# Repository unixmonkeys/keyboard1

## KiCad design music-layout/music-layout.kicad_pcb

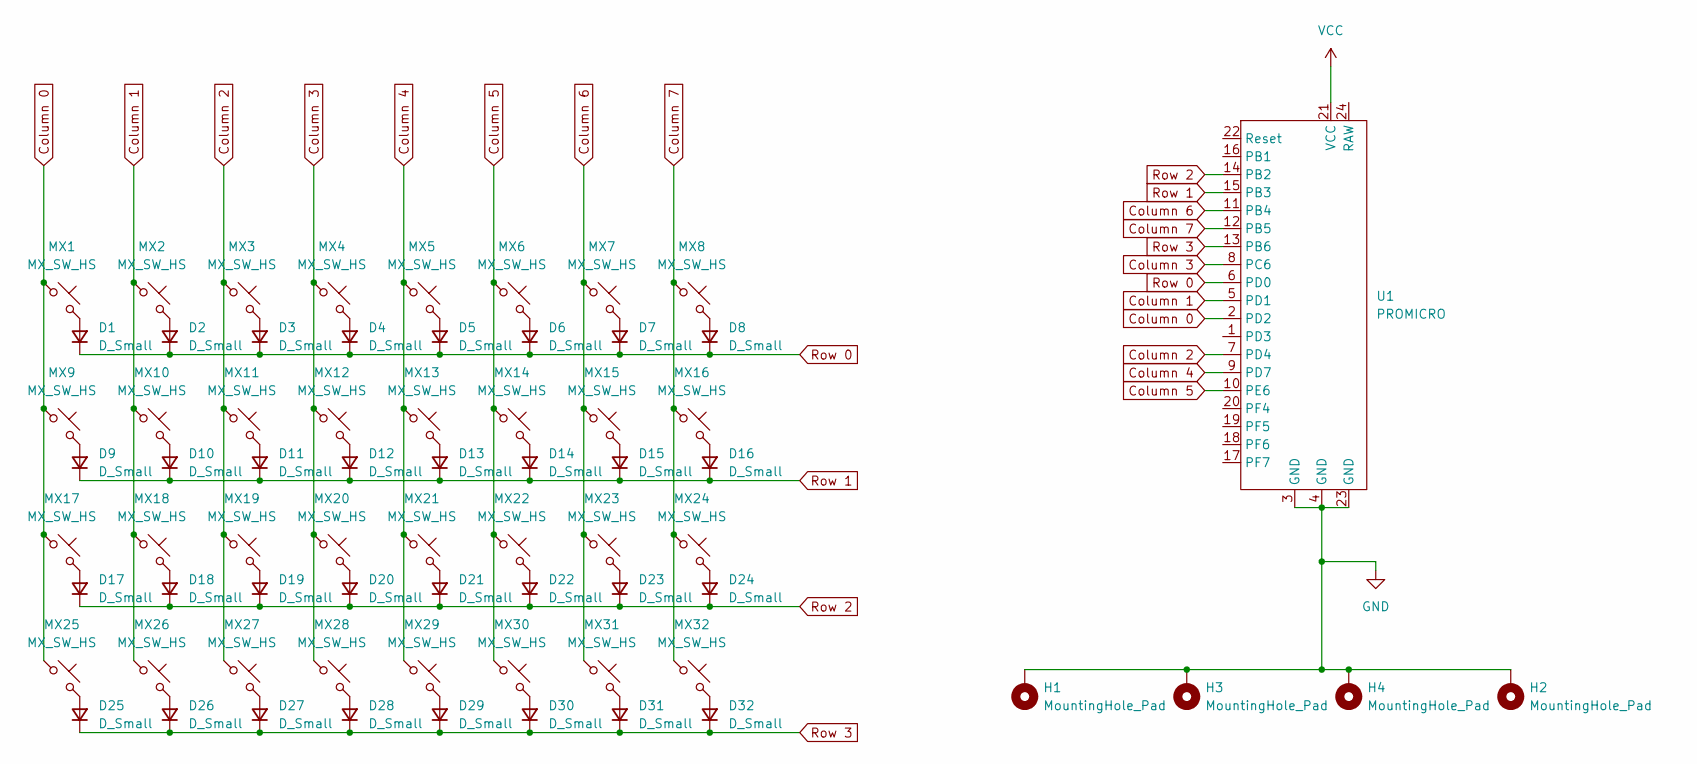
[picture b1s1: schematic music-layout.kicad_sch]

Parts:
D1, D2, D3, D4, D5, D6, D7, D8, D9, D10, D11, D12, D13, D14, D15, D16, D17, D18, D19, D20, D21, D22, D23, D24, D25, D26, D27, D28, D29, D30, D31, D32: D_Small; D_DO-35_SOD27_P7.62mm_Horizontal
H1, H2, H3, H4: MountingHole_Pad; MountingHole_2.2mm_M2_Pad_Via
MX1, MX2, MX3, MX4, MX5, MX6, MX7, MX8, MX9, MX10, MX11, MX12, MX13, MX14, MX15, MX16, MX17, MX18, MX19, MX20, MX21, MX22, MX23, MX24, MX25, MX26, MX27, MX28, MX29, MX30, MX31, MX32: MX_SW_HS; SW_MX_HS_CPG151101S11_1u
U1: PROMICRO; Sparkfun_Pro_Micro

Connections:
Column 0: MX1.1, MX9.1, MX17.1, MX25.1, U1.2 (PD2)
Column 1: MX2.1, MX10.1, MX18.1, MX26.1, U1.5 (PD1)
Column 2: MX3.1, MX11.1, MX19.1, MX27.1, U1.7 (PD4)
Column 3: MX4.1, MX12.1, MX20.1, MX28.1, U1.8 (PC6)
Column 4: MX5.1, MX13.1, MX21.1, MX29.1, U1.9 (PD7)
Column 5: MX6.1, MX14.1, MX22.1, MX30.1, U1.10 (PE6)
Column 6: MX7.1, MX15.1, MX23.1, MX31.1, U1.11 (PB4)
Column 7: MX8.1, MX16.1, MX24.1, MX32.1, U1.12 (PB5)
GND: H1.1, H2.1, H3.1, H4.1, U1.3 (GND), U1.4 (GND), U1.23 (GND)
unnamed: D1.2 (A), MX1.2
unnamed: D2.2 (A), MX2.2
unnamed: D3.2 (A), MX3.2
unnamed: D4.2 (A), MX4.2
unnamed: D5.2 (A), MX5.2
unnamed: D6.2 (A), MX6.2
unnamed: D7.2 (A), MX7.2
unnamed: D8.2 (A), MX8.2
unnamed: D9.2 (A), MX9.2
unnamed: D10.2 (A), MX10.2
unnamed: D11.2 (A), MX11.2
unnamed: D12.2 (A), MX12.2
unnamed: D13.2 (A), MX13.2
unnamed: D14.2 (A), MX14.2
unnamed: D15.2 (A), MX15.2
unnamed: D16.2 (A), MX16.2
unnamed: D17.2 (A), MX17.2
unnamed: D18.2 (A), MX18.2
unnamed: D19.2 (A), MX19.2
unnamed: D20.2 (A), MX20.2
unnamed: D21.2 (A), MX21.2
unnamed: D22.2 (A), MX22.2
unnamed: D23.2 (A), MX23.2
unnamed: D24.2 (A), MX24.2
unnamed: D25.2 (A), MX25.2
unnamed: D26.2 (A), MX26.2
unnamed: D27.2 (A), MX27.2
unnamed: D28.2 (A), MX28.2
unnamed: D29.2 (A), MX29.2
unnamed: D30.2 (A), MX30.2
unnamed: D31.2 (A), MX31.2
unnamed: D32.2 (A), MX32.2
Row 0: D1.1 (K), D2.1 (K), D3.1 (K), D4.1 (K), D5.1 (K), D6.1 (K), D7.1 (K), D8.1 (K), U1.6 (PD0)
Row 1: D9.1 (K), D10.1 (K), D11.1 (K), D12.1 (K), D13.1 (K), D14.1 (K), D15.1 (K), D16.1 (K), U1.15 (PB3)
Row 2: D17.1 (K), D18.1 (K), D19.1 (K), D20.1 (K), D21.1 (K), D22.1 (K), D23.1 (K), D24.1 (K), U1.14 (PB2)
Row 3: D25.1 (K), D26.1 (K), D27.1 (K), D28.1 (K), D29.1 (K), D30.1 (K), D31.1 (K), D32.1 (K), U1.13 (PB6)
VCC: U1.21 (VCC)

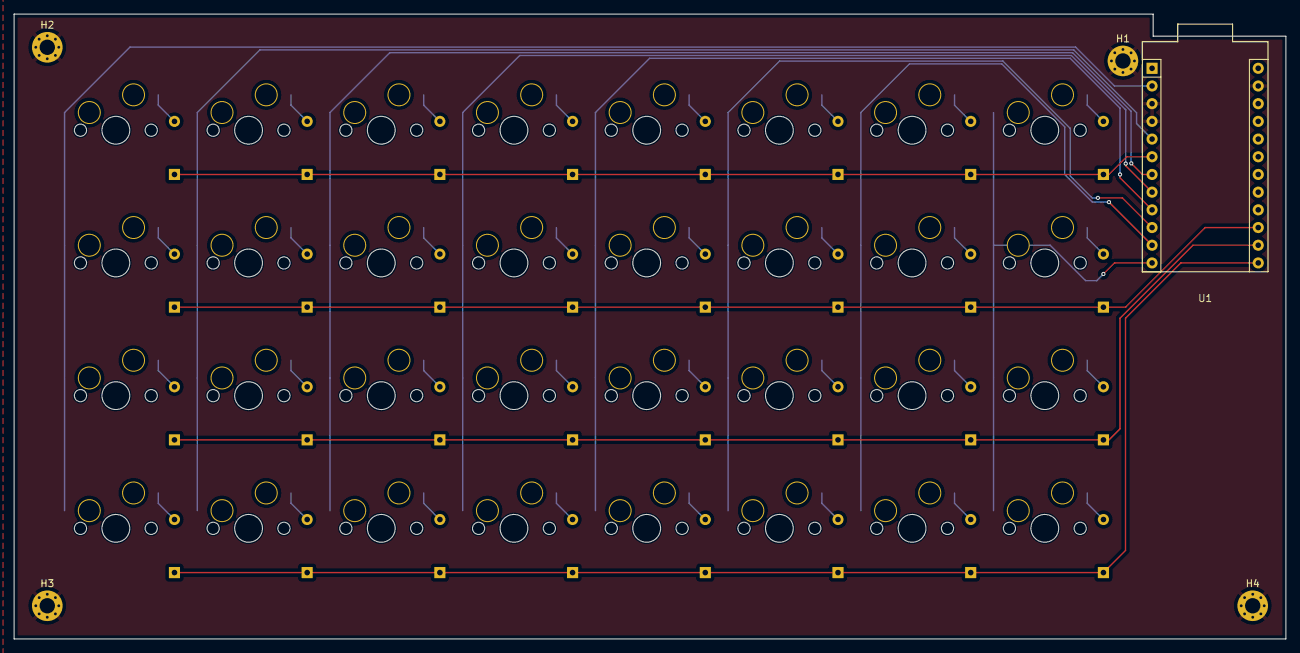
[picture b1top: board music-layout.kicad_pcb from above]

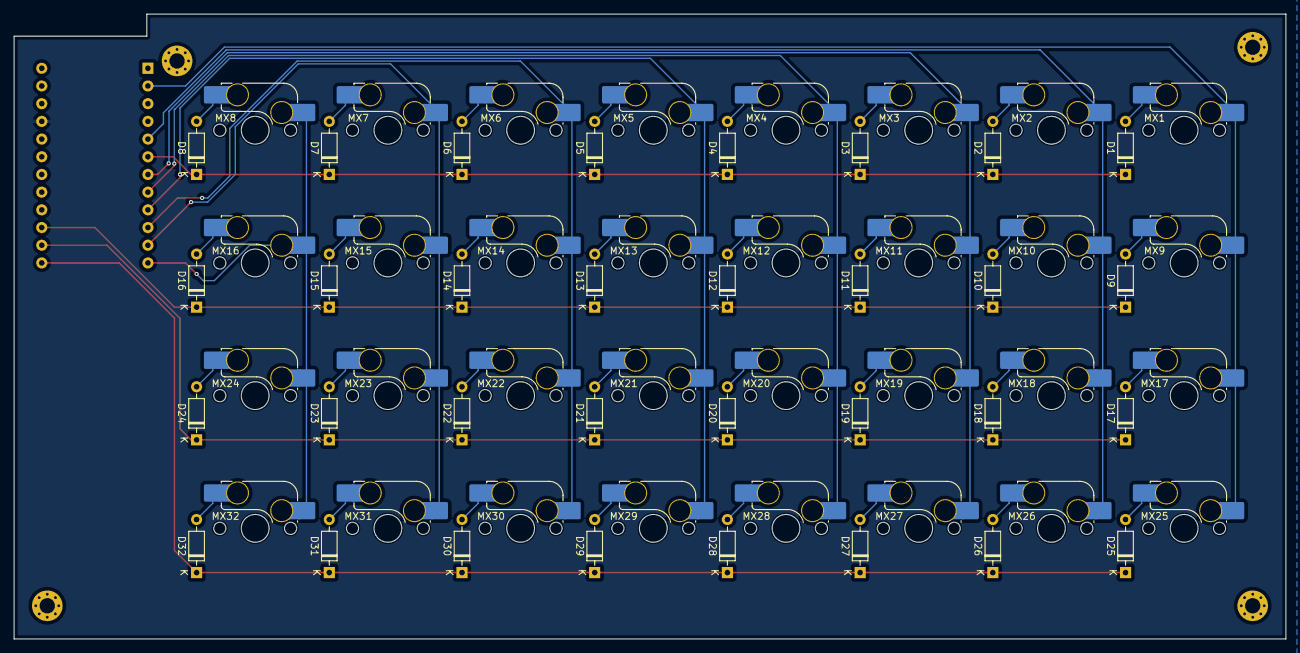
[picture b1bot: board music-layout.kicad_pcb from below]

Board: 2 copper layers, 182.6 x 89.7 mm, 69 parts (64 on the bottom side), 45 nets.

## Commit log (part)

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2024-03-31 Adding keyboard layout
2026-01-18 Add music layout
2026-01-18 Change mode of keyboard-layout.json
2026-01-18 Layout update music-layout.json
2026-04-16 Saving existing keyboard
